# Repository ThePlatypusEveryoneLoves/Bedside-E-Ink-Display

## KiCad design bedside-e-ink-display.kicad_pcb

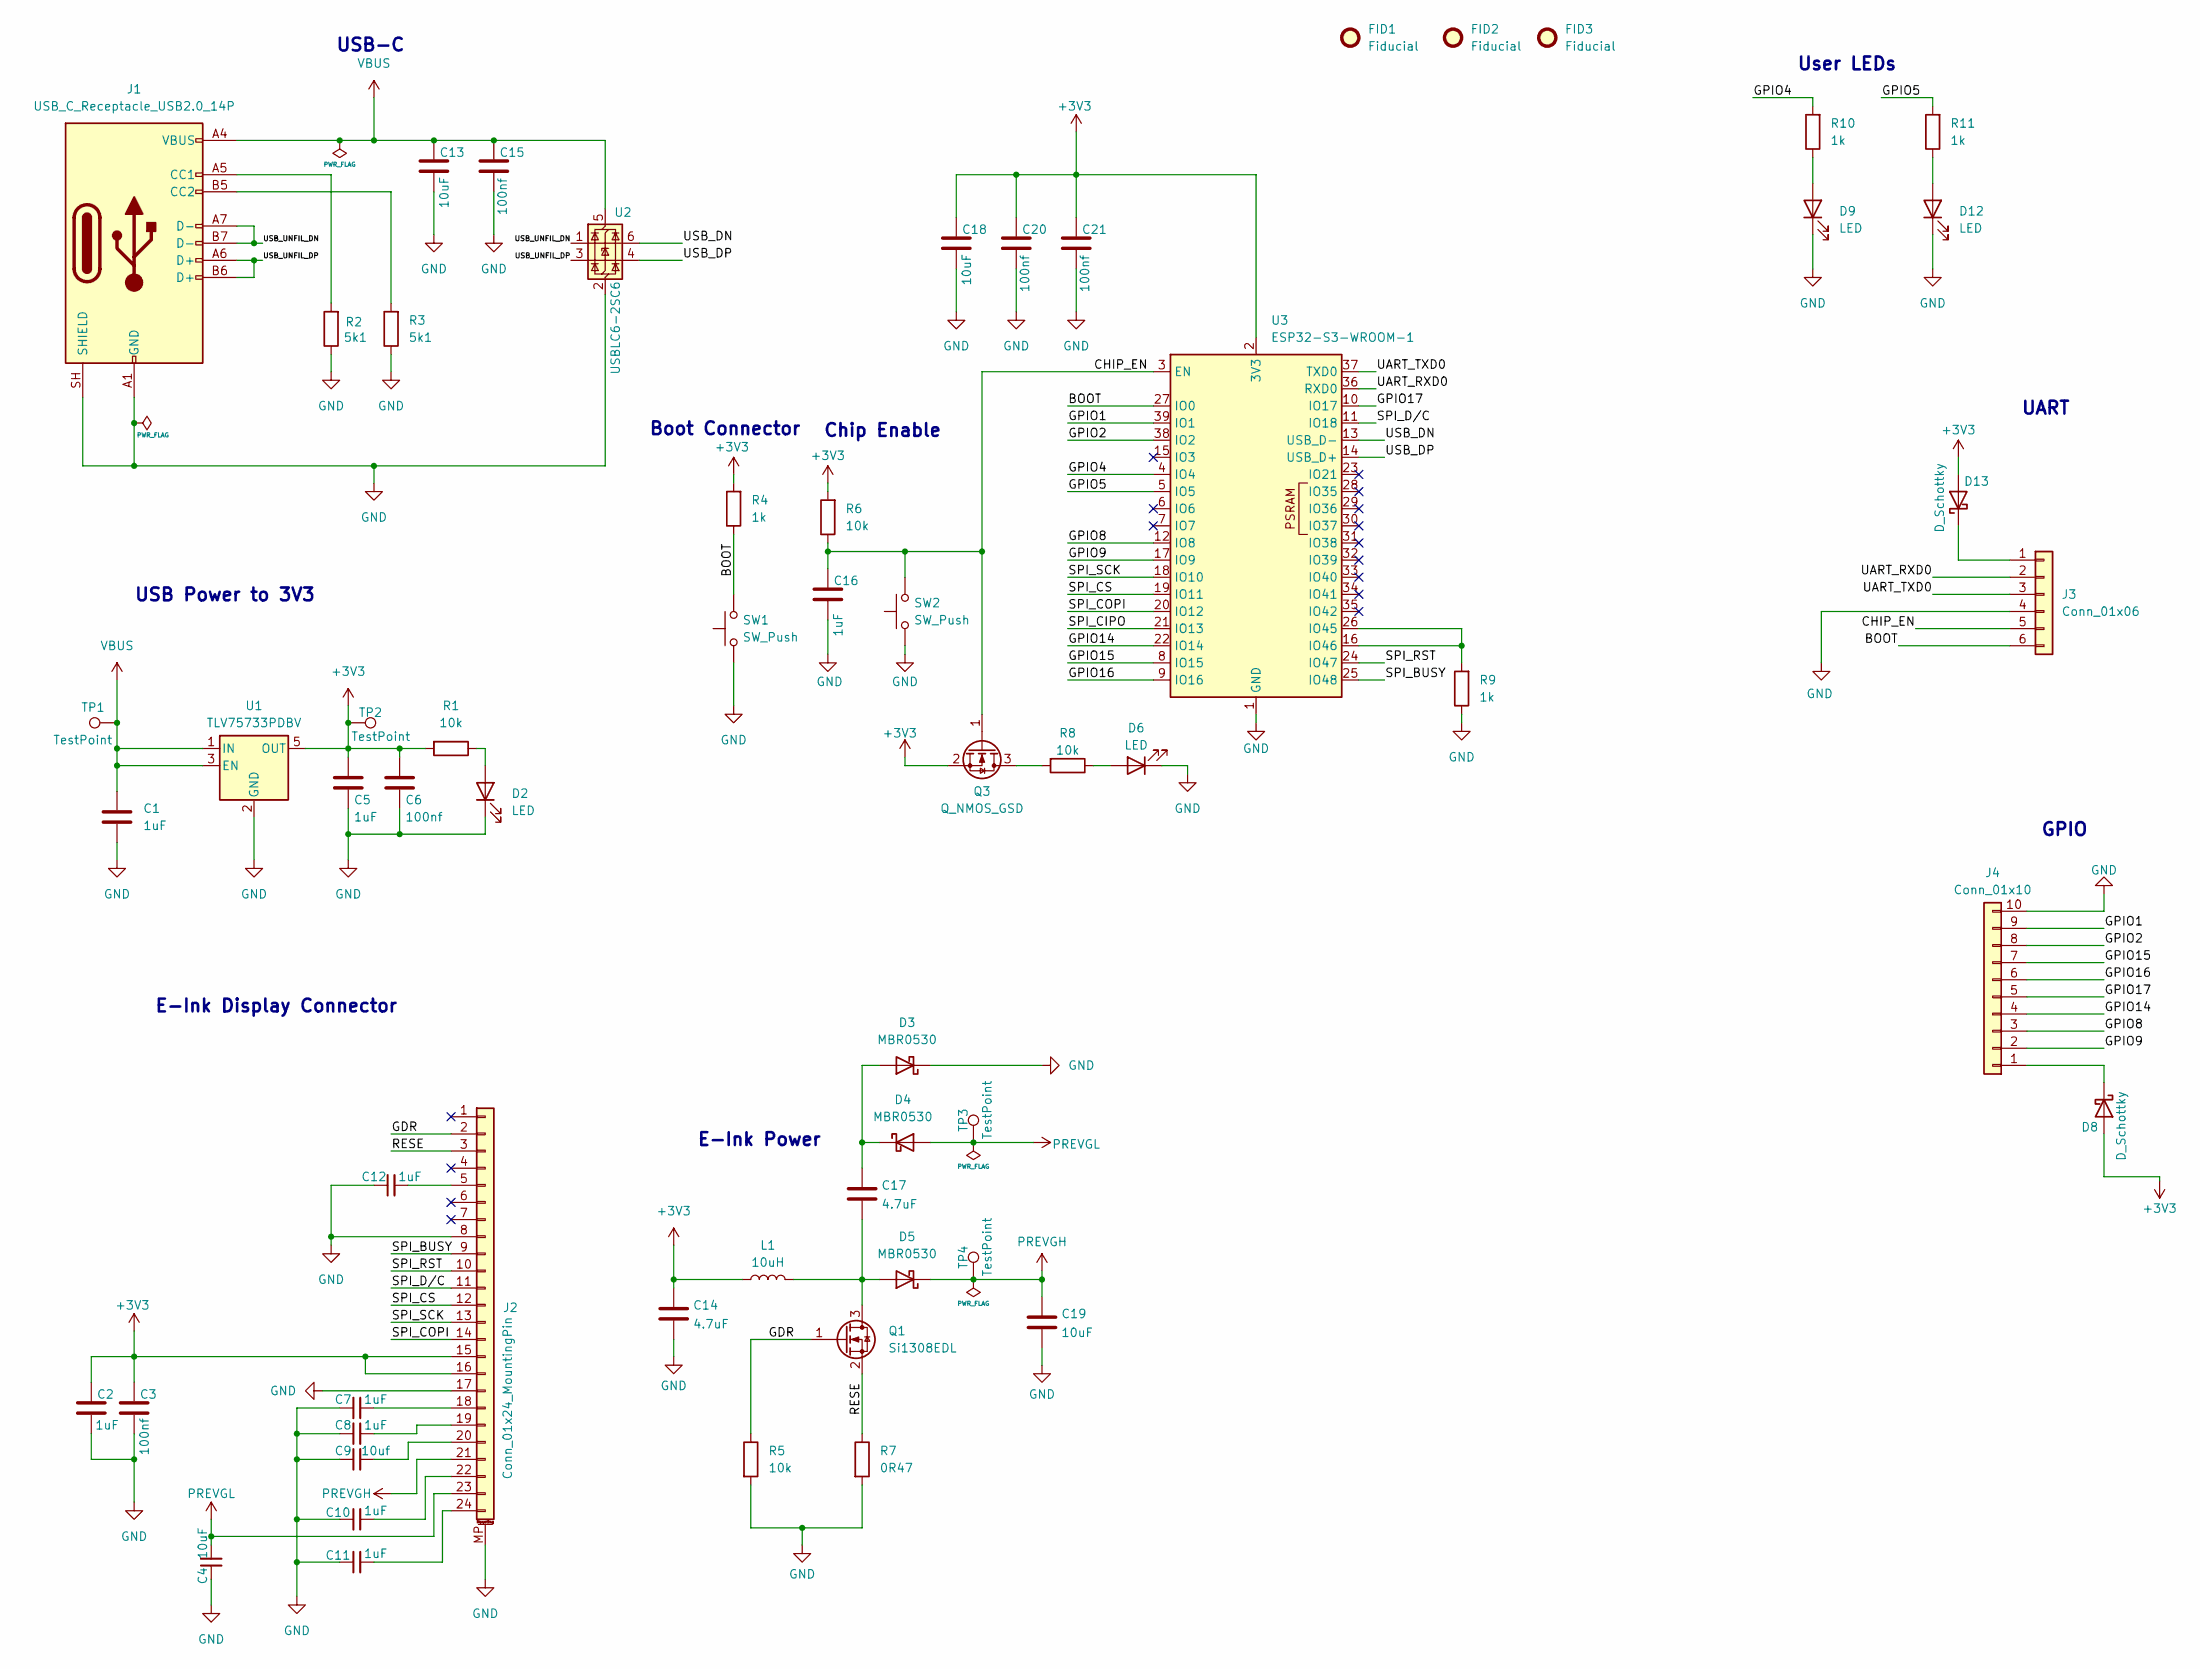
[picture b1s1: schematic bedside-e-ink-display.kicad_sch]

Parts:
C1: 1uF; C_0603_1608Metric; LCSC C15849
C2, C5, C7, C8, C10, C11, C12, C16: 1uF; C_0603_1608Metric; LCSC C1592
C3, C6, C15, C20, C21: 100nf; C_0603_1608Metric
C4, C13, C18, C19: 10uF; C_0603_1608Metric
C9: 10uf; C_0603_1608Metric
C14, C17: 4.7uF; C_0603_1608Metric
D2, D6, D9, D12: LED; LED_0805_2012Metric
D3, D4, D5: MBR0530; D_SOD-123
D8, D13: D_Schottky; D_SOD-323
FID1, FID2, FID3: Fiducial; Fiducial_0.5mm_Mask1mm
J1: USB_C_Receptacle_USB2.0_14P; USB_C_Receptacle_HRO_TYPE-C-31-M-12
J2: Conn_01x24_MountingPin; Hirose_FH12-24S-0.5SH_1x24-1MP_P0.50mm_Horizontal
J3: Conn_01x06; PinHeader_1x06_P2.54mm_Vertical
J4: Conn_01x10; PinHeader_1x10_P2.54mm_Vertical
L1: 10uH; L_Vishay_IHLP-2525
Q1: Si1308EDL; SOT-323_SC-70
Q3: Q_NMOS_GSD; SOT-23
R1, R5, R6, R8: 10k; R_0603_1608Metric
R2, R3: 5k1; R_0603_1608Metric
R4, R9, R10, R11: 1k; R_0603_1608Metric
R7: 0R47; R_0603_1608Metric
SW1, SW2: SW_Push; SW_Push_SPST_NO_Alps_SKRK
TP1, TP2, TP3, TP4: TestPoint; TestPoint_Pad_D1.0mm
U1: TLV75733PDBV; SOT-23-5
U2: USBLC6-2SC6; SOT-23-6
U3: ESP32-S3-WROOM-1

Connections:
+3V3: C2.1, C3.1, C5.1, C6.1, C14.1, C18.1, C20.1, C21.1, D8.2 (A), D13.2 (A), J2.15, J2.16, L1.1, Q3.2 (S), R1.2, R4.2, R6.2, TP2.1, U1.5 (OUT), U3.2 (3V3); also elsewhere on the board
/BOOT: J3.6, R4.1, SW1.2, U3.27 (IO0)
/CHIP_EN: C16.1, J3.5, Q3.1 (G), R6.1, SW2.2, U3.3 (EN)
/GDR: J2.2, Q1.1 (G), R5.1
/GPIO1: J4.9, U3.39 (IO1)
/GPIO2: J4.8, U3.38 (IO2)
/GPIO4: R10.2, U3.4 (IO4)
/GPIO5: R11.2, U3.5 (IO5)
/GPIO8: J4.3, U3.12 (IO8)
/GPIO9: J4.2, U3.17 (IO9)
/GPIO14: J4.4, U3.22 (IO14)
/GPIO15: J4.7, U3.8 (IO15)
/GPIO16: J4.6, U3.9 (IO16)
/GPIO17: J4.5, U3.10 (IO17)
/RESE: J2.3, Q1.2 (S), R7.1
/SPI_BUSY: J2.9, U3.25 (IO48)
/SPI_CIPO: U3.21 (IO13)
/SPI_COPI: J2.14, U3.20 (IO12)
/SPI_CS: J2.12, U3.19 (IO11)
/SPI_D/C: J2.11, U3.11 (IO18)
/SPI_RST: J2.10, U3.24 (IO47)
/SPI_SCK: J2.13, U3.18 (IO10)
/UART_RXD0: J3.2, U3.36 (RXD0)
/UART_TXD0: J3.3, U3.37 (TXD0)
/USB_DN: U2.6 (I/O1), U3.13 (USB_D-)
/USB_DP: U2.4 (I/O2), U3.14 (USB_D+)
/USB_UNFIL_DN: J1.A7 (D-), J1.B7 (D-), U2.1 (I/O1)
/USB_UNFIL_DP: J1.A6 (D+), J1.B6 (D+), U2.3 (I/O2)
GND: C1.2, C2.2, C3.2, C4.1, C5.2, C6.2, C7.1, C8.1, C9.1, C10.1, C11.1, C12.1, C13.2, C14.2, C15.2, C16.2, C18.2, C19.2, C20.2, C21.2, D2.1 (K), D3.1 (K), D6.1 (K), D9.1 (K), D12.1 (K), J1.A1 (GND), J1.A12 (GND), J1.B1 (GND), J1.B12 (GND), J1.SH (SHIELD), J2.8, J2.17, J2.MP (MountPin), J3.4, J4.10, R2.1, R3.1, R5.2, R7.2, R9.1, SW1.1, SW2.1, U1.2 (GND), U2.2 (GND), U3.1 (GND), U3.40 (GND), U3.41 (GND)
unnamed: D2.2 (A), R1.1
unnamed: C17.1, D3.2 (A), D4.1 (K)
unnamed: C17.2, D5.2 (A), L1.2, Q1.3 (D)
unnamed: D6.2 (A), R8.1
unnamed: D8.1 (K), J4.1
unnamed: D9.2 (A), R10.1
unnamed: D12.2 (A), R11.1
unnamed: D13.1 (K), J3.1
unnamed: J1.A5 (CC1), R2.2
unnamed: J1.B5 (CC2), R3.2
unnamed: C12.2, J2.5
unnamed: C7.2, J2.18
unnamed: C8.2, J2.19
unnamed: C9.2, J2.20
unnamed: C10.2, J2.22
unnamed: C11.2, J2.24
unnamed: Q3.3 (D), R8.2
unnamed: R9.2, U3.16 (IO46), U3.26 (IO45)
PREVGH: C19.1, D5.1 (K), J2.21, TP4.1 (1_1)
PREVGL: C4.2, D4.2 (A), J2.23, TP3.1 (1_1)
VBUS: C1.1, C13.1, C15.1, J1.A4 (VBUS), J1.A9 (VBUS), J1.B4 (VBUS), J1.B9 (VBUS), TP1.1, U1.1 (IN), U1.3 (EN), U2.5 (VBUS); also elsewhere on the board

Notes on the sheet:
Boot Connector
USB Power to 3V3
E-Ink Power
E-Ink Display Connector
User LEDs
UART
Chip Enable
USB-C
GPIO

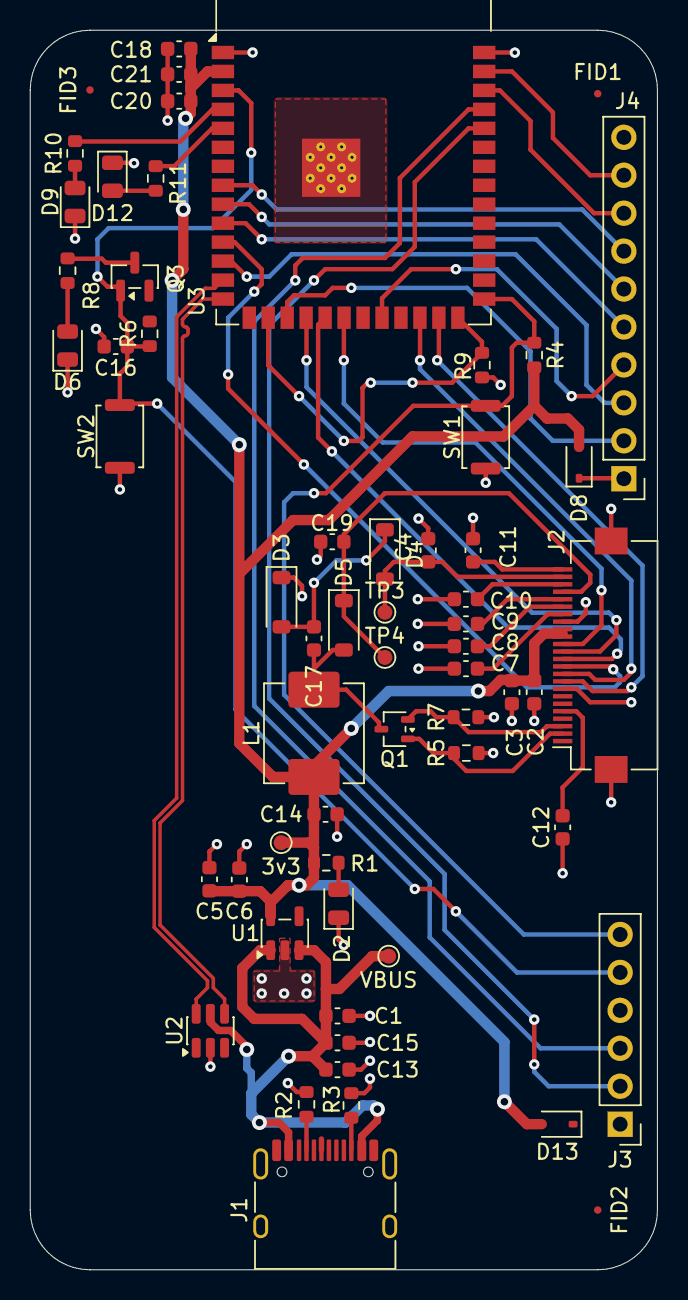
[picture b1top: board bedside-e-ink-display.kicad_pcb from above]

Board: 4 copper layers, 42.0 x 83.0 mm, 60 parts (0 on the bottom side), 49 nets.

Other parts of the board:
3v3: TestPoint; TestPoint_Pad_D1.0mm
VBUS: TestPoint; TestPoint_Pad_D1.0mm

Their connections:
+3V3: 3v3.1 (1_1); also elsewhere on the board
VBUS: VBUS.1 (1_1); also elsewhere on the board
